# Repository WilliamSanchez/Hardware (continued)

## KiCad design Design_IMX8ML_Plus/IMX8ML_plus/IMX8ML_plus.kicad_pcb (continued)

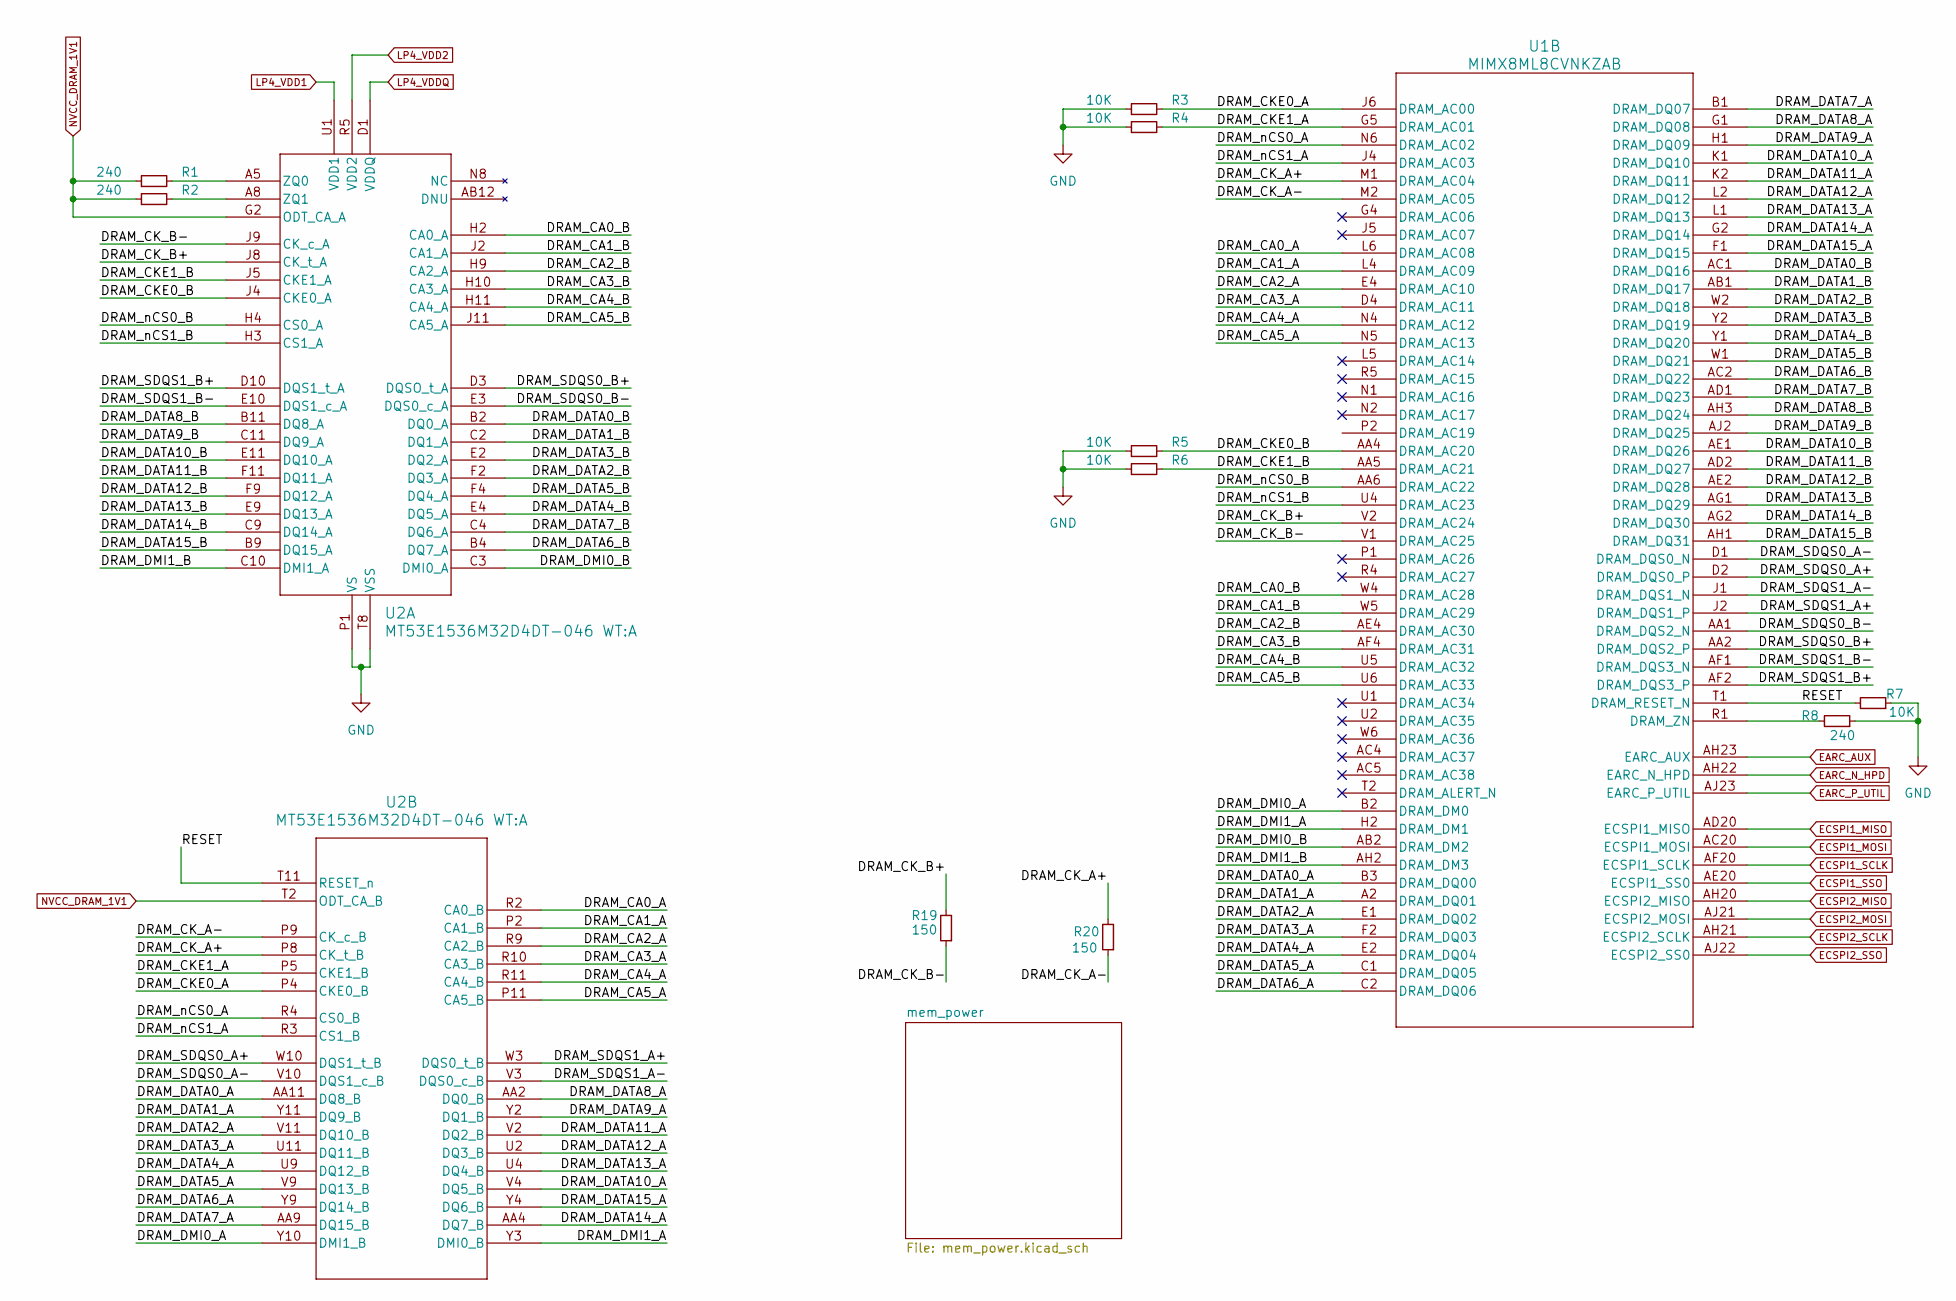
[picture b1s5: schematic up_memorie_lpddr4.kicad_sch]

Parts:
R1, R2, R8: 240; R_0201_0603Metric
R3, R4, R5, R6, R7: 10K; R_0201_0603Metric
R19, R20: 150; R_0201_0603Metric
U1: MIMX8ML8CVNKZAB; LFBGA548_SOT2047-1_NXP
U2: MT53E1536M32D4DT-046 WT:A; VFBGA200_10X14-5_DT_MRN

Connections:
/Processor/Up_memorie_lpddr4/DRAM_CA0_A: U1.L6 (DRAM_AC08), U2.R2 (CA0_B)
/Processor/Up_memorie_lpddr4/DRAM_CA0_B: U1.W4 (DRAM_AC28), U2.H2 (CA0_A)
/Processor/Up_memorie_lpddr4/DRAM_CA1_A: U1.L4 (DRAM_AC09), U2.P2 (CA1_B)
/Processor/Up_memorie_lpddr4/DRAM_CA1_B: U1.W5 (DRAM_AC29), U2.J2 (CA1_A)
/Processor/Up_memorie_lpddr4/DRAM_CA2_A: U1.E4 (DRAM_AC10), U2.R9 (CA2_B)
/Processor/Up_memorie_lpddr4/DRAM_CA2_B: U1.AE4 (DRAM_AC30), U2.H9 (CA2_A)
/Processor/Up_memorie_lpddr4/DRAM_CA3_A: U1.D4 (DRAM_AC11), U2.R10 (CA3_B)
/Processor/Up_memorie_lpddr4/DRAM_CA3_B: U1.AF4 (DRAM_AC31), U2.H10 (CA3_A)
/Processor/Up_memorie_lpddr4/DRAM_CA4_A: U1.N4 (DRAM_AC12), U2.R11 (CA4_B)
/Processor/Up_memorie_lpddr4/DRAM_CA4_B: U1.U5 (DRAM_AC32), U2.H11 (CA4_A)
/Processor/Up_memorie_lpddr4/DRAM_CA5_A: U1.N5 (DRAM_AC13), U2.P11 (CA5_B)
/Processor/Up_memorie_lpddr4/DRAM_CA5_B: U1.U6 (DRAM_AC33), U2.J11 (CA5_A)
/Processor/Up_memorie_lpddr4/DRAM_CKE0_A: R3.2, U1.J6 (DRAM_AC00), U2.P4 (CKE0_B)
/Processor/Up_memorie_lpddr4/DRAM_CKE0_B: R5.2, U1.AA4 (DRAM_AC20), U2.J4 (CKE0_A)
/Processor/Up_memorie_lpddr4/DRAM_CKE1_A: R4.2, U1.G5 (DRAM_AC01), U2.P5 (CKE1_B)
/Processor/Up_memorie_lpddr4/DRAM_CKE1_B: R6.2, U1.AA5 (DRAM_AC21), U2.J5 (CKE1_A)
/Processor/Up_memorie_lpddr4/DRAM_CK_A+: R20.2, U1.M1 (DRAM_AC04), U2.P8 (CK_t_B)
/Processor/Up_memorie_lpddr4/DRAM_CK_A-: R20.1, U1.M2 (DRAM_AC05), U2.P9 (CK_c_B)
/Processor/Up_memorie_lpddr4/DRAM_CK_B+: R19.2, U1.V2 (DRAM_AC24), U2.J8 (CK_t_A)
/Processor/Up_memorie_lpddr4/DRAM_CK_B-: R19.1, U1.V1 (DRAM_AC25), U2.J9 (CK_c_A)
/Processor/Up_memorie_lpddr4/DRAM_DATA0_A: U1.B3 (DRAM_DQ00), U2.AA11 (DQ8_B)
/Processor/Up_memorie_lpddr4/DRAM_DATA0_B: U1.AC1 (DRAM_DQ16), U2.B2 (DQ0_A)
/Processor/Up_memorie_lpddr4/DRAM_DATA1_A: U1.A2 (DRAM_DQ01), U2.Y11 (DQ9_B)
/Processor/Up_memorie_lpddr4/DRAM_DATA1_B: U1.AB1 (DRAM_DQ17), U2.C2 (DQ1_A)
/Processor/Up_memorie_lpddr4/DRAM_DATA2_A: U1.E1 (DRAM_DQ02), U2.V11 (DQ10_B)
/Processor/Up_memorie_lpddr4/DRAM_DATA2_B: U1.W2 (DRAM_DQ18), U2.F2 (DQ3_A)
/Processor/Up_memorie_lpddr4/DRAM_DATA3_A: U1.F2 (DRAM_DQ03), U2.U11 (DQ11_B)
/Processor/Up_memorie_lpddr4/DRAM_DATA3_B: U1.Y2 (DRAM_DQ19), U2.E2 (DQ2_A)
/Processor/Up_memorie_lpddr4/DRAM_DATA4_A: U1.E2 (DRAM_DQ04), U2.U9 (DQ12_B)
/Processor/Up_memorie_lpddr4/DRAM_DATA4_B: U1.Y1 (DRAM_DQ20), U2.E4 (DQ5_A)
/Processor/Up_memorie_lpddr4/DRAM_DATA5_A: U1.C1 (DRAM_DQ05), U2.V9 (DQ13_B)
/Processor/Up_memorie_lpddr4/DRAM_DATA5_B: U1.W1 (DRAM_DQ21), U2.F4 (DQ4_A)
/Processor/Up_memorie_lpddr4/DRAM_DATA6_A: U1.C2 (DRAM_DQ06), U2.Y9 (DQ14_B)
/Processor/Up_memorie_lpddr4/DRAM_DATA6_B: U1.AC2 (DRAM_DQ22), U2.B4 (DQ7_A)
/Processor/Up_memorie_lpddr4/DRAM_DATA7_A: U1.B1 (DRAM_DQ07), U2.AA9 (DQ15_B)
/Processor/Up_memorie_lpddr4/DRAM_DATA7_B: U1.AD1 (DRAM_DQ23), U2.C4 (DQ6_A)
/Processor/Up_memorie_lpddr4/DRAM_DATA8_A: U1.G1 (DRAM_DQ08), U2.AA2 (DQ0_B)
/Processor/Up_memorie_lpddr4/DRAM_DATA8_B: U1.AH3 (DRAM_DQ24), U2.B11 (DQ8_A)
/Processor/Up_memorie_lpddr4/DRAM_DATA9_A: U1.H1 (DRAM_DQ09), U2.Y2 (DQ1_B)
/Processor/Up_memorie_lpddr4/DRAM_DATA9_B: U1.AJ2 (DRAM_DQ25), U2.C11 (DQ9_A)
/Processor/Up_memorie_lpddr4/DRAM_DATA10_A: U1.K1 (DRAM_DQ10), U2.V4 (DQ5_B)
/Processor/Up_memorie_lpddr4/DRAM_DATA10_B: U1.AE1 (DRAM_DQ26), U2.E11 (DQ10_A)
/Processor/Up_memorie_lpddr4/DRAM_DATA11_A: U1.K2 (DRAM_DQ11), U2.V2 (DQ2_B)
/Processor/Up_memorie_lpddr4/DRAM_DATA11_B: U1.AD2 (DRAM_DQ27), U2.F11 (DQ11_A)
/Processor/Up_memorie_lpddr4/DRAM_DATA12_A: U1.L2 (DRAM_DQ12), U2.U2 (DQ3_B)
/Processor/Up_memorie_lpddr4/DRAM_DATA12_B: U1.AE2 (DRAM_DQ28), U2.F9 (DQ12_A)
/Processor/Up_memorie_lpddr4/DRAM_DATA13_A: U1.L1 (DRAM_DQ13), U2.U4 (DQ4_B)
/Processor/Up_memorie_lpddr4/DRAM_DATA13_B: U1.AG1 (DRAM_DQ29), U2.E9 (DQ13_A)
/Processor/Up_memorie_lpddr4/DRAM_DATA14_A: U1.G2 (DRAM_DQ14), U2.AA4 (DQ7_B)
/Processor/Up_memorie_lpddr4/DRAM_DATA14_B: U1.AG2 (DRAM_DQ30), U2.C9 (DQ14_A)
/Processor/Up_memorie_lpddr4/DRAM_DATA15_A: U1.F1 (DRAM_DQ15), U2.Y4 (DQ6_B)
/Processor/Up_memorie_lpddr4/DRAM_DATA15_B: U1.AH1 (DRAM_DQ31), U2.B9 (DQ15_A)
/Processor/Up_memorie_lpddr4/DRAM_DMI0_A: U1.B2 (DRAM_DM0), U2.Y10 (DMI1_B)
/Processor/Up_memorie_lpddr4/DRAM_DMI0_B: U1.AB2 (DRAM_DM2), U2.C3 (DMI0_A)
/Processor/Up_memorie_lpddr4/DRAM_DMI1_A: U1.H2 (DRAM_DM1), U2.Y3 (DMI0_B)
/Processor/Up_memorie_lpddr4/DRAM_DMI1_B: U1.AH2 (DRAM_DM3), U2.C10 (DMI1_A)
/Processor/Up_memorie_lpddr4/DRAM_SDQS0_A+: U1.D2 (DRAM_DQS0_P), U2.W10 (DQS1_t_B)
/Processor/Up_memorie_lpddr4/DRAM_SDQS0_A-: U1.D1 (DRAM_DQS0_N), U2.V10 (DQS1_c_B)
/Processor/Up_memorie_lpddr4/DRAM_SDQS0_B+: U1.AA2 (DRAM_DQS2_P), U2.D3 (DQSO_t_A)
/Processor/Up_memorie_lpddr4/DRAM_SDQS0_B-: U1.AA1 (DRAM_DQS2_N), U2.E3 (DQS0_c_A)
/Processor/Up_memorie_lpddr4/DRAM_SDQS1_A+: U1.J2 (DRAM_DQS1_P), U2.W3 (DQS0_t_B)
/Processor/Up_memorie_lpddr4/DRAM_SDQS1_A-: U1.J1 (DRAM_DQS1_N), U2.V3 (DQS0_c_B)
/Processor/Up_memorie_lpddr4/DRAM_SDQS1_B+: U1.AF2 (DRAM_DQS3_P), U2.D10 (DQS1_t_A)
/Processor/Up_memorie_lpddr4/DRAM_SDQS1_B-: U1.AF1 (DRAM_DQS3_N), U2.E10 (DQS1_c_A)
/Processor/Up_memorie_lpddr4/DRAM_nCS0_A: U1.N6 (DRAM_AC02), U2.R4 (CS0_B)
/Processor/Up_memorie_lpddr4/DRAM_nCS0_B: U1.AA6 (DRAM_AC22), U2.H4 (CS0_A)
/Processor/Up_memorie_lpddr4/DRAM_nCS1_A: U1.J4 (DRAM_AC03), U2.R3 (CS1_B)
/Processor/Up_memorie_lpddr4/DRAM_nCS1_B: U1.U4 (DRAM_AC23), U2.H3 (CS1_A)
/Processor/Up_memorie_lpddr4/RESET: R7.2, U1.T1 (DRAM_RESET_N), U2.T11 (RESET_n)
EARC_AUX: U1.AH23 (EARC_AUX); also elsewhere on the board
EARC_N_HPD: U1.AH22 (EARC_N_HPD); also elsewhere on the board
EARC_P_UTIL: U1.AJ23 (EARC_P_UTIL); also elsewhere on the board
ECSPI1_MISO: U1.AD20 (ECSPI1_MISO); also elsewhere on the board
ECSPI1_MOSI: U1.AC20 (ECSPI1_MOSI); also elsewhere on the board
ECSPI1_SCLK: U1.AF20 (ECSPI1_SCLK); also elsewhere on the board
ECSPI1_SSO: U1.AE20 (ECSPI1_SS0); also elsewhere on the board
ECSPI2_MISO: U1.AH20 (ECSPI2_MISO); also elsewhere on the board
ECSPI2_MOSI: U1.AJ21 (ECSPI2_MOSI); also elsewhere on the board
ECSPI2_SCLK: U1.AH21 (ECSPI2_SCLK); also elsewhere on the board
ECSPI2_SSO: U1.AJ22 (ECSPI2_SS0); also elsewhere on the board
GND: R3.1, R4.1, R5.1, R6.1, R7.1, R8.1, U2.A3 (VSS), U2.A10 (VSS), U2.AB3 (VSS), U2.AB5 (VSS), U2.AB8 (VSS), U2.AB10 (VSS), U2.C1 (VSS), U2.C5 (VSS), U2.C8 (VSS), U2.C12 (VSS), U2.D2 (VSS), U2.D4 (VSS), U2.D9 (VSS), U2.D11 (VSS), U2.E1 (VSS), U2.E5 (VSS), U2.E8 (VSS), U2.E12 (VSS), U2.G1 (VSS), U2.G3 (VSS), U2.G5 (VSS), U2.G8 (VSS), U2.G10 (VSS), U2.G12 (VSS), U2.J1 (VSS), U2.J3 (VSS), U2.J10 (VSS), U2.J12 (VSS), U2.K2 (VSS), U2.K4 (VSS), U2.K9 (VSS), U2.K11 (VSS), U2.N2 (VSS), U2.N4 (VSS), U2.N9 (VSS), U2.N11 (VSS), U2.P1 (VS), U2.P3 (VSS), U2.P10 (VSS), U2.P12 (VSS), U2.T1 (VSS), U2.T3 (VSS), U2.T5 (VSS), U2.T8 (VSS), U2.T10 (VSS), U2.T12 (VSS), U2.V1 (VSS), U2.V5 (VSS), U2.V8 (VSS), U2.V12 (VSS), U2.W2 (VSS), U2.W4 (VSS), U2.W9 (VSS), U2.W11 (VSS), U2.Y1 (VSS), U2.Y5 (VSS), U2.Y8 (VSS), U2.Y12 (VSS); also elsewhere on the board
LP4_VDD1: U2.F1 (VDD1), U2.F12 (VDD1), U2.G4 (VDD1), U2.G9 (VDD1), U2.T4 (VDD1), U2.T9 (VDD1), U2.U1 (VDD1), U2.U12 (VDD1); also elsewhere on the board
LP4_VDD2: R1.1, R2.1, U2.A4 (VDD2), U2.A9 (VDD2), U2.AA3 (VDDQ), U2.AA5 (VDDQ), U2.AA8 (VDDQ), U2.AA10 (VDDQ), U2.AB4 (VDD2), U2.AB9 (VDD2), U2.B3 (VDDQ), U2.B5 (VDDQ), U2.B8 (VDDQ), U2.B10 (VDDQ), U2.D1 (VDDQ), U2.D5 (VDDQ), U2.D8 (VDDQ), U2.D12 (VDDQ), U2.F3 (VDDQ), U2.F5 (VDD2), U2.F8 (VDD2), U2.F10 (VDDQ), U2.G2 (ODT_CA_A), U2.H1 (VDD2), U2.H5 (VDD2), U2.H8 (VDD2), U2.H12 (VDD2), U2.K1 (VDD2), U2.K3 (VDD2), U2.K10 (VDD2), U2.K12 (VDD2), U2.N1 (VDD2), U2.N3 (VDD2), U2.N10 (VDD2), U2.N12 (VDD2), U2.R1 (VDD2), U2.R5 (VDD2), U2.R8 (VDD2), U2.R12 (VDD2), U2.T2 (ODT_CA_B), U2.U3 (VDDQ), U2.U5 (VDD2), U2.U8 (VDD2), U2.U10 (VDDQ), U2.W1 (VDDQ), U2.W5 (VDDQ), U2.W8 (VDDQ), U2.W12 (VDDQ); also elsewhere on the board
unnamed: R8.2, U1.R1 (DRAM_ZN)
unnamed: R1.2, U2.A5 (ZQ0)
unnamed: R2.2, U2.A8 (ZQ1)

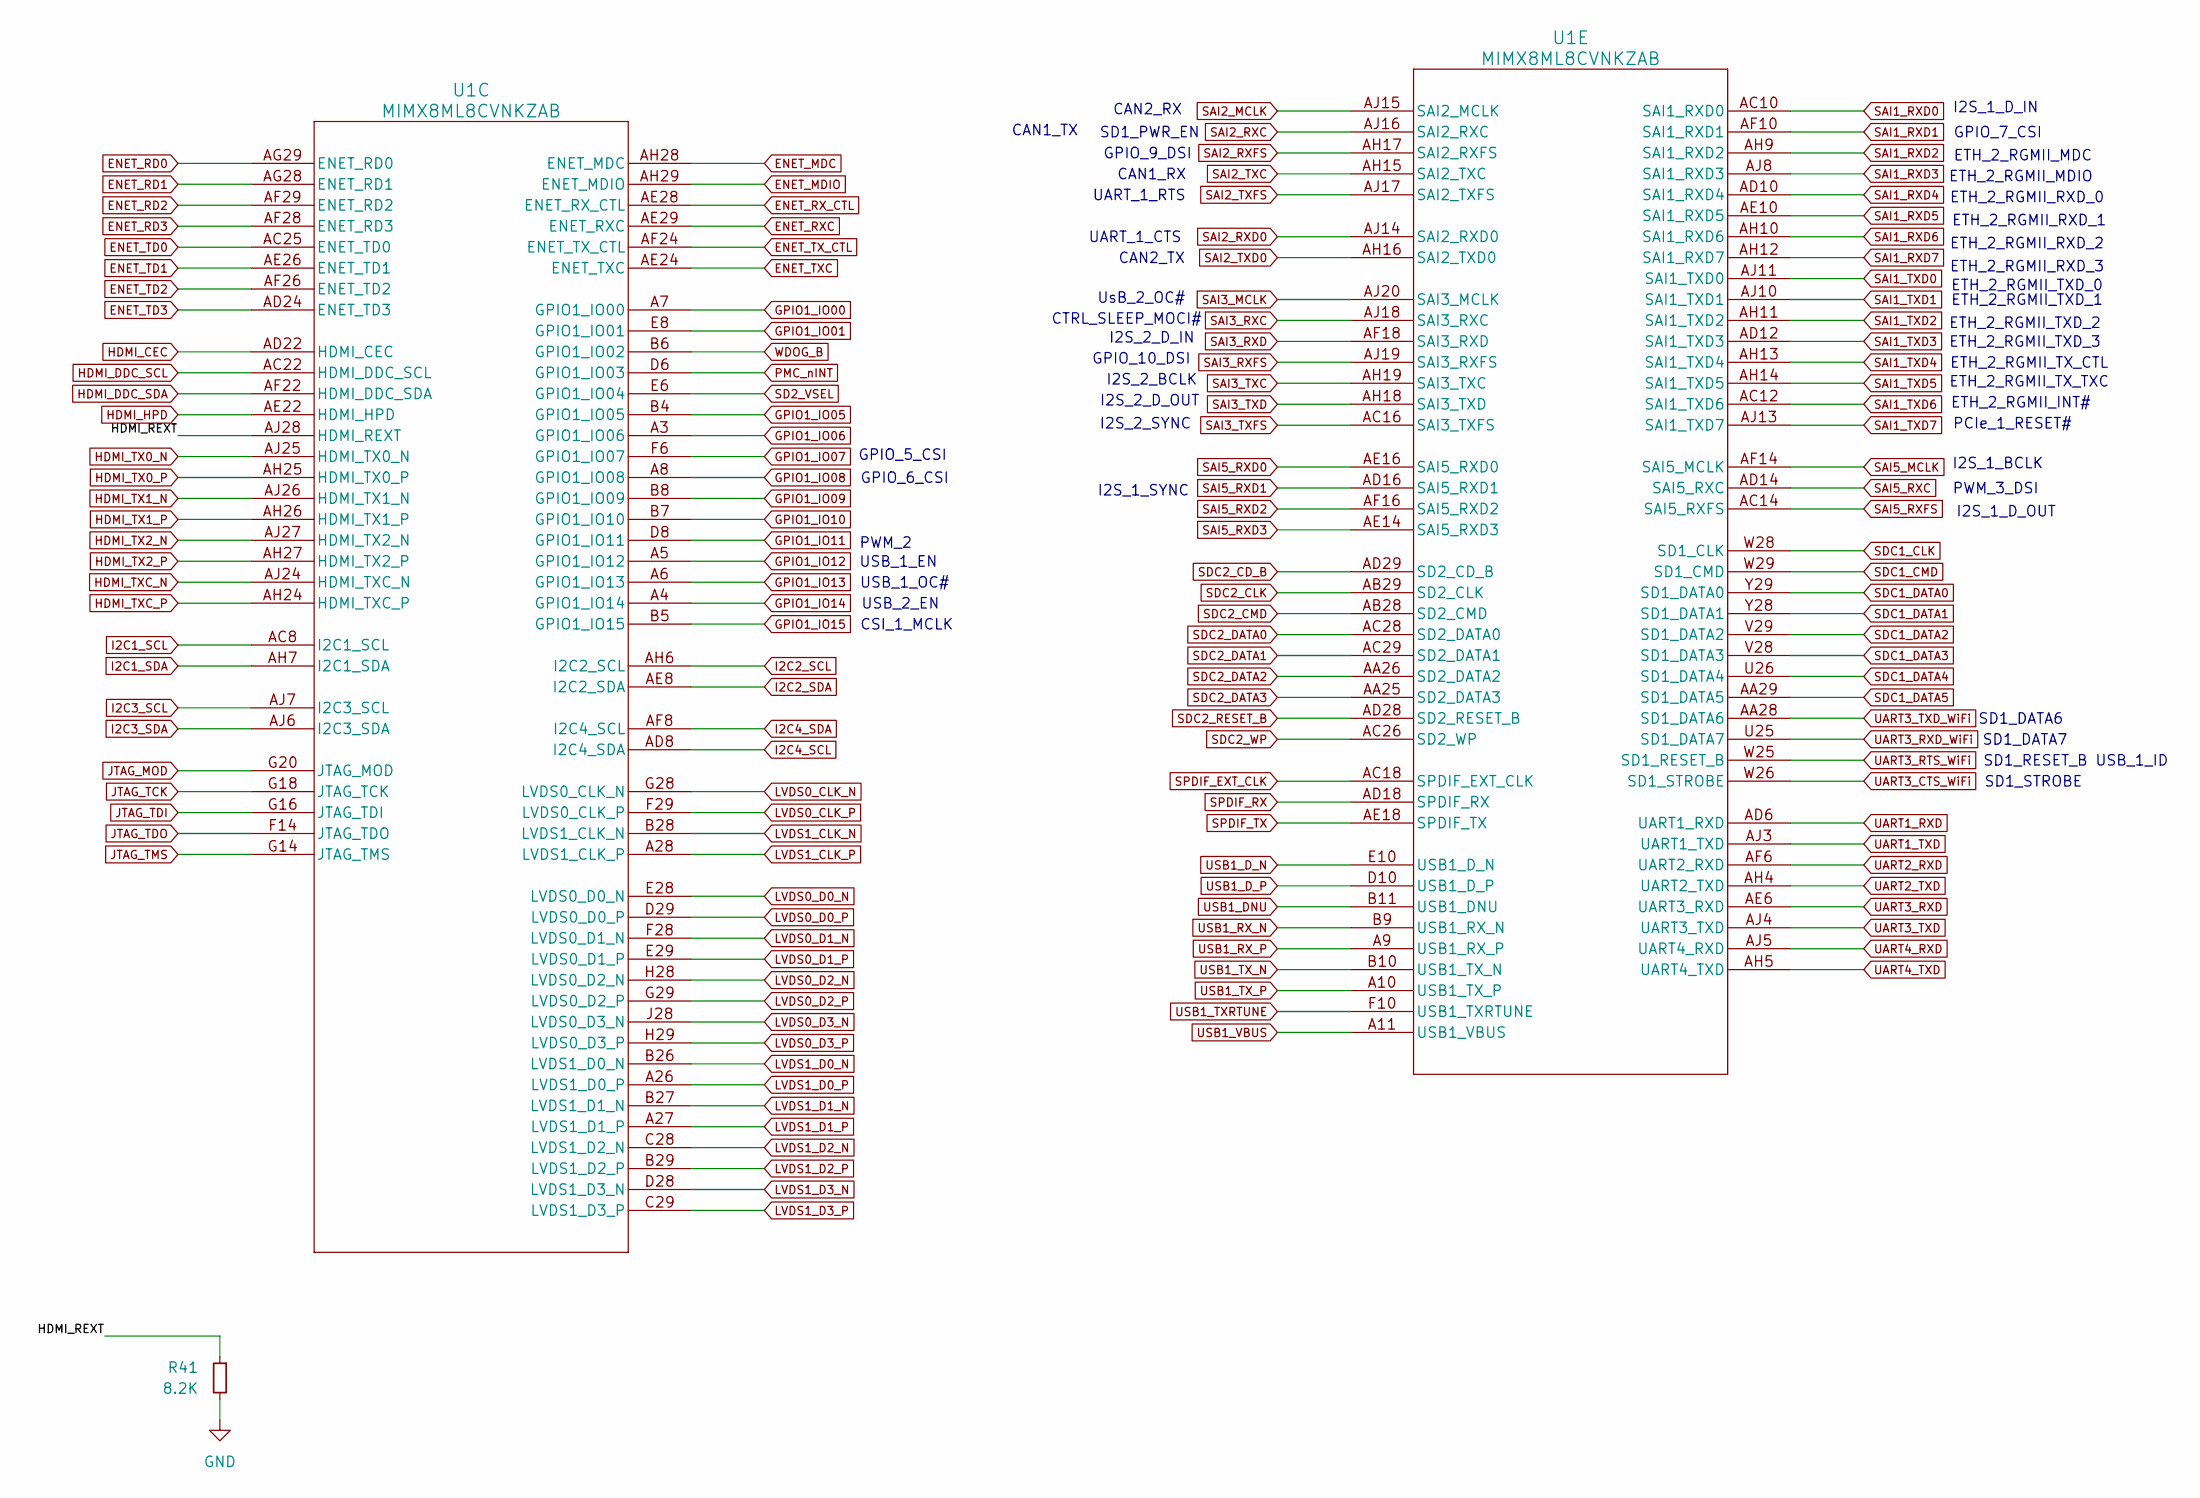
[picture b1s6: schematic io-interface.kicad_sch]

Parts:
R41: 8.2K; R_0201_0603Metric
U1: MIMX8ML8CVNKZAB; LFBGA548_SOT2047-1_NXP

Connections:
/Processor/io-interface/<NO NET>: R41.1, U1.AJ28 (HDMI_REXT)
ENET_MDC: U1.AH28 (ENET_MDC); also elsewhere on the board
ENET_MDIO: U1.AH29 (ENET_MDIO); also elsewhere on the board
ENET_RD0: U1.AG29 (ENET_RD0); also elsewhere on the board
ENET_RD1: U1.AG28 (ENET_RD1); also elsewhere on the board
ENET_RD2: U1.AF29 (ENET_RD2); also elsewhere on the board
ENET_RD3: U1.AF28 (ENET_RD3); also elsewhere on the board
ENET_RXC: U1.AE29 (ENET_RXC); also elsewhere on the board
ENET_RX_CTL: U1.AE28 (ENET_RX_CTL); also elsewhere on the board
ENET_TD0: U1.AC25 (ENET_TD0); also elsewhere on the board
ENET_TD1: U1.AE26 (ENET_TD1); also elsewhere on the board
ENET_TD2: U1.AF26 (ENET_TD2); also elsewhere on the board
ENET_TD3: U1.AD24 (ENET_TD3); also elsewhere on the board
ENET_TXC: U1.AE24 (ENET_TXC); also elsewhere on the board
ENET_TX_CTL: U1.AF24 (ENET_TX_CTL); also elsewhere on the board
GND: R41.2; also elsewhere on the board
GPIO1_IO00: U1.A7 (GPIO1_IO00); also elsewhere on the board
GPIO1_IO01: U1.E8 (GPIO1_IO01); also elsewhere on the board
GPIO1_IO05: U1.B4 (GPIO1_IO05); also elsewhere on the board
GPIO1_IO06: U1.A3 (GPIO1_IO06); also elsewhere on the board
GPIO1_IO07: U1.F6 (GPIO1_IO07); also elsewhere on the board
GPIO1_IO08: U1.A8 (GPIO1_IO08); also elsewhere on the board
GPIO1_IO09: U1.B8 (GPIO1_IO09); also elsewhere on the board
GPIO1_IO10: U1.B7 (GPIO1_IO10); also elsewhere on the board
GPIO1_IO11: U1.D8 (GPIO1_IO11); also elsewhere on the board
GPIO1_IO12: U1.A5 (GPIO1_IO12); also elsewhere on the board
GPIO1_IO13: U1.A6 (GPIO1_IO13); also elsewhere on the board
GPIO1_IO14: U1.A4 (GPIO1_IO14); also elsewhere on the board
GPIO1_IO15: U1.B5 (GPIO1_IO15); also elsewhere on the board
HDMI_CEC: U1.AD22 (HDMI_CEC); also elsewhere on the board
HDMI_DDC_SCL: U1.AC22 (HDMI_DDC_SCL); also elsewhere on the board
HDMI_DDC_SDA: U1.AF22 (HDMI_DDC_SDA); also elsewhere on the board
HDMI_HPD: U1.AE22 (HDMI_HPD); also elsewhere on the board
HDMI_TX0_N: U1.AJ25 (HDMI_TX0_N); also elsewhere on the board
HDMI_TX0_P: U1.AH25 (HDMI_TX0_P); also elsewhere on the board
HDMI_TX1_N: U1.AJ26 (HDMI_TX1_N); also elsewhere on the board
HDMI_TX1_P: U1.AH26 (HDMI_TX1_P); also elsewhere on the board
HDMI_TX2_N: U1.AJ27 (HDMI_TX2_N); also elsewhere on the board
HDMI_TX2_P: U1.AH27 (HDMI_TX2_P); also elsewhere on the board
HDMI_TXC_N: U1.AJ24 (HDMI_TXC_N); also elsewhere on the board
HDMI_TXC_P: U1.AH24 (HDMI_TXC_P); also elsewhere on the board
I2C1_SCL: U1.AC8 (I2C1_SCL); also elsewhere on the board
I2C1_SDA: U1.AH7 (I2C1_SDA); also elsewhere on the board
I2C2_SCL: U1.AH6 (I2C2_SCL); also elsewhere on the board
I2C2_SDA: U1.AE8 (I2C2_SDA); also elsewhere on the board
I2C3_SCL: U1.AJ7 (I2C3_SCL); also elsewhere on the board
I2C3_SDA: U1.AJ6 (I2C3_SDA); also elsewhere on the board
I2C4_SCL: U1.AD8 (I2C4_SDA); also elsewhere on the board
I2C4_SDA: U1.AF8 (I2C4_SCL); also elsewhere on the board
JTAG_MOD: U1.G20 (JTAG_MOD); also elsewhere on the board
JTAG_TCK: U1.G18 (JTAG_TCK); also elsewhere on the board
JTAG_TDI: U1.G16 (JTAG_TDI); also elsewhere on the board
JTAG_TDO: U1.F14 (JTAG_TDO); also elsewhere on the board
JTAG_TMS: U1.G14 (JTAG_TMS); also elsewhere on the board
LVDS0_CLK_N: U1.G28 (LVDS0_CLK_N); also elsewhere on the board
LVDS0_CLK_P: U1.F29 (LVDS0_CLK_P); also elsewhere on the board
LVDS0_D0_N: U1.E28 (LVDS0_D0_N); also elsewhere on the board
LVDS0_D0_P: U1.D29 (LVDS0_D0_P); also elsewhere on the board
LVDS0_D1_N: U1.F28 (LVDS0_D1_N); also elsewhere on the board
LVDS0_D1_P: U1.E29 (LVDS0_D1_P); also elsewhere on the board
LVDS0_D2_N: U1.H28 (LVDS0_D2_N); also elsewhere on the board
LVDS0_D2_P: U1.G29 (LVDS0_D2_P); also elsewhere on the board
LVDS0_D3_N: U1.J28 (LVDS0_D3_N); also elsewhere on the board
LVDS0_D3_P: U1.H29 (LVDS0_D3_P); also elsewhere on the board
LVDS1_CLK_N: U1.B28 (LVDS1_CLK_N); also elsewhere on the board
LVDS1_CLK_P: U1.A28 (LVDS1_CLK_P); also elsewhere on the board
LVDS1_D0_N: U1.B26 (LVDS1_D0_N); also elsewhere on the board
LVDS1_D0_P: U1.A26 (LVDS1_D0_P); also elsewhere on the board
LVDS1_D1_N: U1.B27 (LVDS1_D1_N); also elsewhere on the board
LVDS1_D1_P: U1.A27 (LVDS1_D1_P); also elsewhere on the board
LVDS1_D2_N: U1.C28 (LVDS1_D2_N); also elsewhere on the board
LVDS1_D2_P: U1.B29 (LVDS1_D2_P); also elsewhere on the board
LVDS1_D3_N: U1.D28 (LVDS1_D3_N); also elsewhere on the board
LVDS1_D3_P: U1.C29 (LVDS1_D3_P); also elsewhere on the board
PMC_nINT: U1.D6 (GPIO1_IO03); also elsewhere on the board
SAI1_RXD0: U1.AC10 (SAI1_RXD0); also elsewhere on the board
SAI1_RXD1: U1.AF10 (SAI1_RXD1); also elsewhere on the board
SAI1_RXD2: U1.AH9 (SAI1_RXD2); also elsewhere on the board
SAI1_RXD3: U1.AJ8 (SAI1_RXD3); also elsewhere on the board
SAI1_RXD4: U1.AD10 (SAI1_RXD4); also elsewhere on the board
SAI1_RXD5: U1.AE10 (SAI1_RXD5); also elsewhere on the board
SAI1_RXD6: U1.AH10 (SAI1_RXD6); also elsewhere on the board
SAI1_RXD7: U1.AH12 (SAI1_RXD7); also elsewhere on the board
SAI1_TXD0: U1.AJ11 (SAI1_TXD0); also elsewhere on the board
SAI1_TXD1: U1.AJ10 (SAI1_TXD1); also elsewhere on the board
SAI1_TXD2: U1.AH11 (SAI1_TXD2); also elsewhere on the board
SAI1_TXD3: U1.AD12 (SAI1_TXD3); also elsewhere on the board
SAI1_TXD4: U1.AH13 (SAI1_TXD4); also elsewhere on the board
SAI1_TXD5: U1.AH14 (SAI1_TXD5); also elsewhere on the board
SAI1_TXD6: U1.AC12 (SAI1_TXD6); also elsewhere on the board
SAI1_TXD7: U1.AJ13 (SAI1_TXD7); also elsewhere on the board
SAI2_MCLK: U1.AJ15 (SAI2_MCLK); also elsewhere on the board
SAI2_RXC: U1.AJ16 (SAI2_RXC); also elsewhere on the board
SAI2_RXD0: U1.AJ14 (SAI2_RXD0); also elsewhere on the board
SAI2_RXFS: U1.AH17 (SAI2_RXFS); also elsewhere on the board
SAI2_TXC: U1.AH15 (SAI2_TXC); also elsewhere on the board
SAI2_TXD0: U1.AH16 (SAI2_TXD0); also elsewhere on the board
SAI2_TXFS: U1.AJ17 (SAI2_TXFS); also elsewhere on the board
SAI3_MCLK: U1.AJ20 (SAI3_MCLK); also elsewhere on the board
SAI3_RXC: U1.AJ18 (SAI3_RXC); also elsewhere on the board
SAI3_RXD: U1.AF18 (SAI3_RXD); also elsewhere on the board
SAI3_RXFS: U1.AJ19 (SAI3_RXFS); also elsewhere on the board
SAI3_TXC: U1.AH19 (SAI3_TXC); also elsewhere on the board
SAI3_TXD: U1.AH18 (SAI3_TXD); also elsewhere on the board
SAI3_TXFS: U1.AC16 (SAI3_TXFS); also elsewhere on the board
SAI5_MCLK: U1.AF14 (SAI5_MCLK); also elsewhere on the board
SAI5_RXC: U1.AD14 (SAI5_RXC); also elsewhere on the board
SAI5_RXD0: U1.AE16 (SAI5_RXD0); also elsewhere on the board
SAI5_RXD1: U1.AD16 (SAI5_RXD1); also elsewhere on the board
SAI5_RXD2: U1.AF16 (SAI5_RXD2); also elsewhere on the board
SAI5_RXD3: U1.AE14 (SAI5_RXD3); also elsewhere on the board
SAI5_RXFS: U1.AC14 (SAI5_RXFS); also elsewhere on the board
SD2_VSEL: U1.E6 (GPIO1_IO04); also elsewhere on the board
SDC1_CLK: U1.W28 (SD1_CLK); also elsewhere on the board
SDC1_CMD: U1.W29 (SD1_CMD); also elsewhere on the board
SDC1_DATA0: U1.Y29 (SD1_DATA0); also elsewhere on the board
SDC1_DATA1: U1.Y28 (SD1_DATA1); also elsewhere on the board
SDC1_DATA2: U1.V29 (SD1_DATA2); also elsewhere on the board
SDC1_DATA3: U1.V28 (SD1_DATA3); also elsewhere on the board
SDC1_DATA4: U1.U26 (SD1_DATA4)
SDC1_DATA5: U1.AA29 (SD1_DATA5)
SDC2_CD_B: U1.AD29 (SD2_CD_B); also elsewhere on the board
SDC2_CLK: U1.AB29 (SD2_CLK); also elsewhere on the board
SDC2_CMD: U1.AB28 (SD2_CMD); also elsewhere on the board
SDC2_DATA0: U1.AC28 (SD2_DATA0); also elsewhere on the board
SDC2_DATA1: U1.AC29 (SD2_DATA1); also elsewhere on the board
SDC2_DATA2: U1.AA26 (SD2_DATA2); also elsewhere on the board
SDC2_DATA3: U1.AA25 (SD2_DATA3); also elsewhere on the board
SDC2_RESET_B: U1.AD28 (SD2_RESET_B); also elsewhere on the board
SDC2_WP: U1.AC26 (SD2_WP); also elsewhere on the board
SPDIF_EXT_CLK: U1.AC18 (SPDIF_EXT_CLK); also elsewhere on the board
SPDIF_RX: U1.AD18 (SPDIF_RX); also elsewhere on the board
SPDIF_TX: U1.AE18 (SPDIF_TX); also elsewhere on the board
UART1_RXD: U1.AD6 (UART1_RXD); also elsewhere on the board
UART1_TXD: U1.AJ3 (UART1_TXD); also elsewhere on the board
UART2_RXD: U1.AF6 (UART2_RXD); also elsewhere on the board
UART2_TXD: U1.AH4 (UART2_TXD); also elsewhere on the board
UART3_CTS_WiFi: U1.W26 (SD1_STROBE); also elsewhere on the board
UART3_RTS_WiFi: U1.W25 (SD1_RESET_B); also elsewhere on the board
UART3_RXD: U1.AE6 (UART3_RXD)
UART3_RXD_WiFi: U1.U25 (SD1_DATA7); also elsewhere on the board
UART3_TXD: U1.AJ4 (UART3_TXD)
UART3_TXD_WiFi: U1.AA28 (SD1_DATA6); also elsewhere on the board
UART4_RXD: U1.AJ5 (UART4_RXD); also elsewhere on the board
UART4_TXD: U1.AH5 (UART4_TXD); also elsewhere on the board
USB1_DNU: U1.B11 (USB1_DNU)
USB1_D_N: U1.E10 (USB1_D_N); also elsewhere on the board
USB1_D_P: U1.D10 (USB1_D_P); also elsewhere on the board
USB1_RX_N: U1.B9 (USB1_RX_N); also elsewhere on the board
USB1_RX_P: U1.A9 (USB1_RX_P); also elsewhere on the board
USB1_TXRTUNE: U1.F10 (USB1_TXRTUNE)
USB1_TX_N: U1.B10 (USB1_TX_N); also elsewhere on the board
USB1_TX_P: U1.A10 (USB1_TX_P); also elsewhere on the board
USB1_VBUS: U1.A11 (USB1_VBUS); also elsewhere on the board
WDOG_B: U1.B6 (GPIO1_IO02); also elsewhere on the board

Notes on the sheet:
CSI_1_MCLK
ETH_2_RGMII_TXD_2
I2S_1_BCLK
SD1_DATA6
CAN2_RX
CAN2_TX
SD1_STROBE
I2S_2_SYNC
PWM_3_DSI
GPIO_5_CSI
PCIe_1_RESET#
ETH_2_RGMII_INT#
ETH_2_RGMII_RXD_0
ETH_2_RGMII_RXD_2
UART_1_CTS
ETH_2_RGMII_TXD_3
SD1_RESET_B
ETH_2_RGMII_TX_TXC
UART_1_RTS
CAN1_RX
ETH_2_RGMII_MDIO
GPIO_6_CSI
PWM_2
I2S_1_D_OUT
I2S_1_D_IN
USB_1_OC#
GPIO_10_DSI
ETH_2_RGMII_TX_CTL
SD1_PWR_EN
ETH_2_RGMII_MDC
GPIO_9_DSI
CAN1_TX
ETH_2_RGMII_TXD_0
I2S_1_SYNC
CTRL_SLEEP_MOCI#
USB_1_EN
ETH_2_RGMII_RXD_1
UsB_2_OC#
USB_2_EN
ETH_2_RGMII_RXD_3

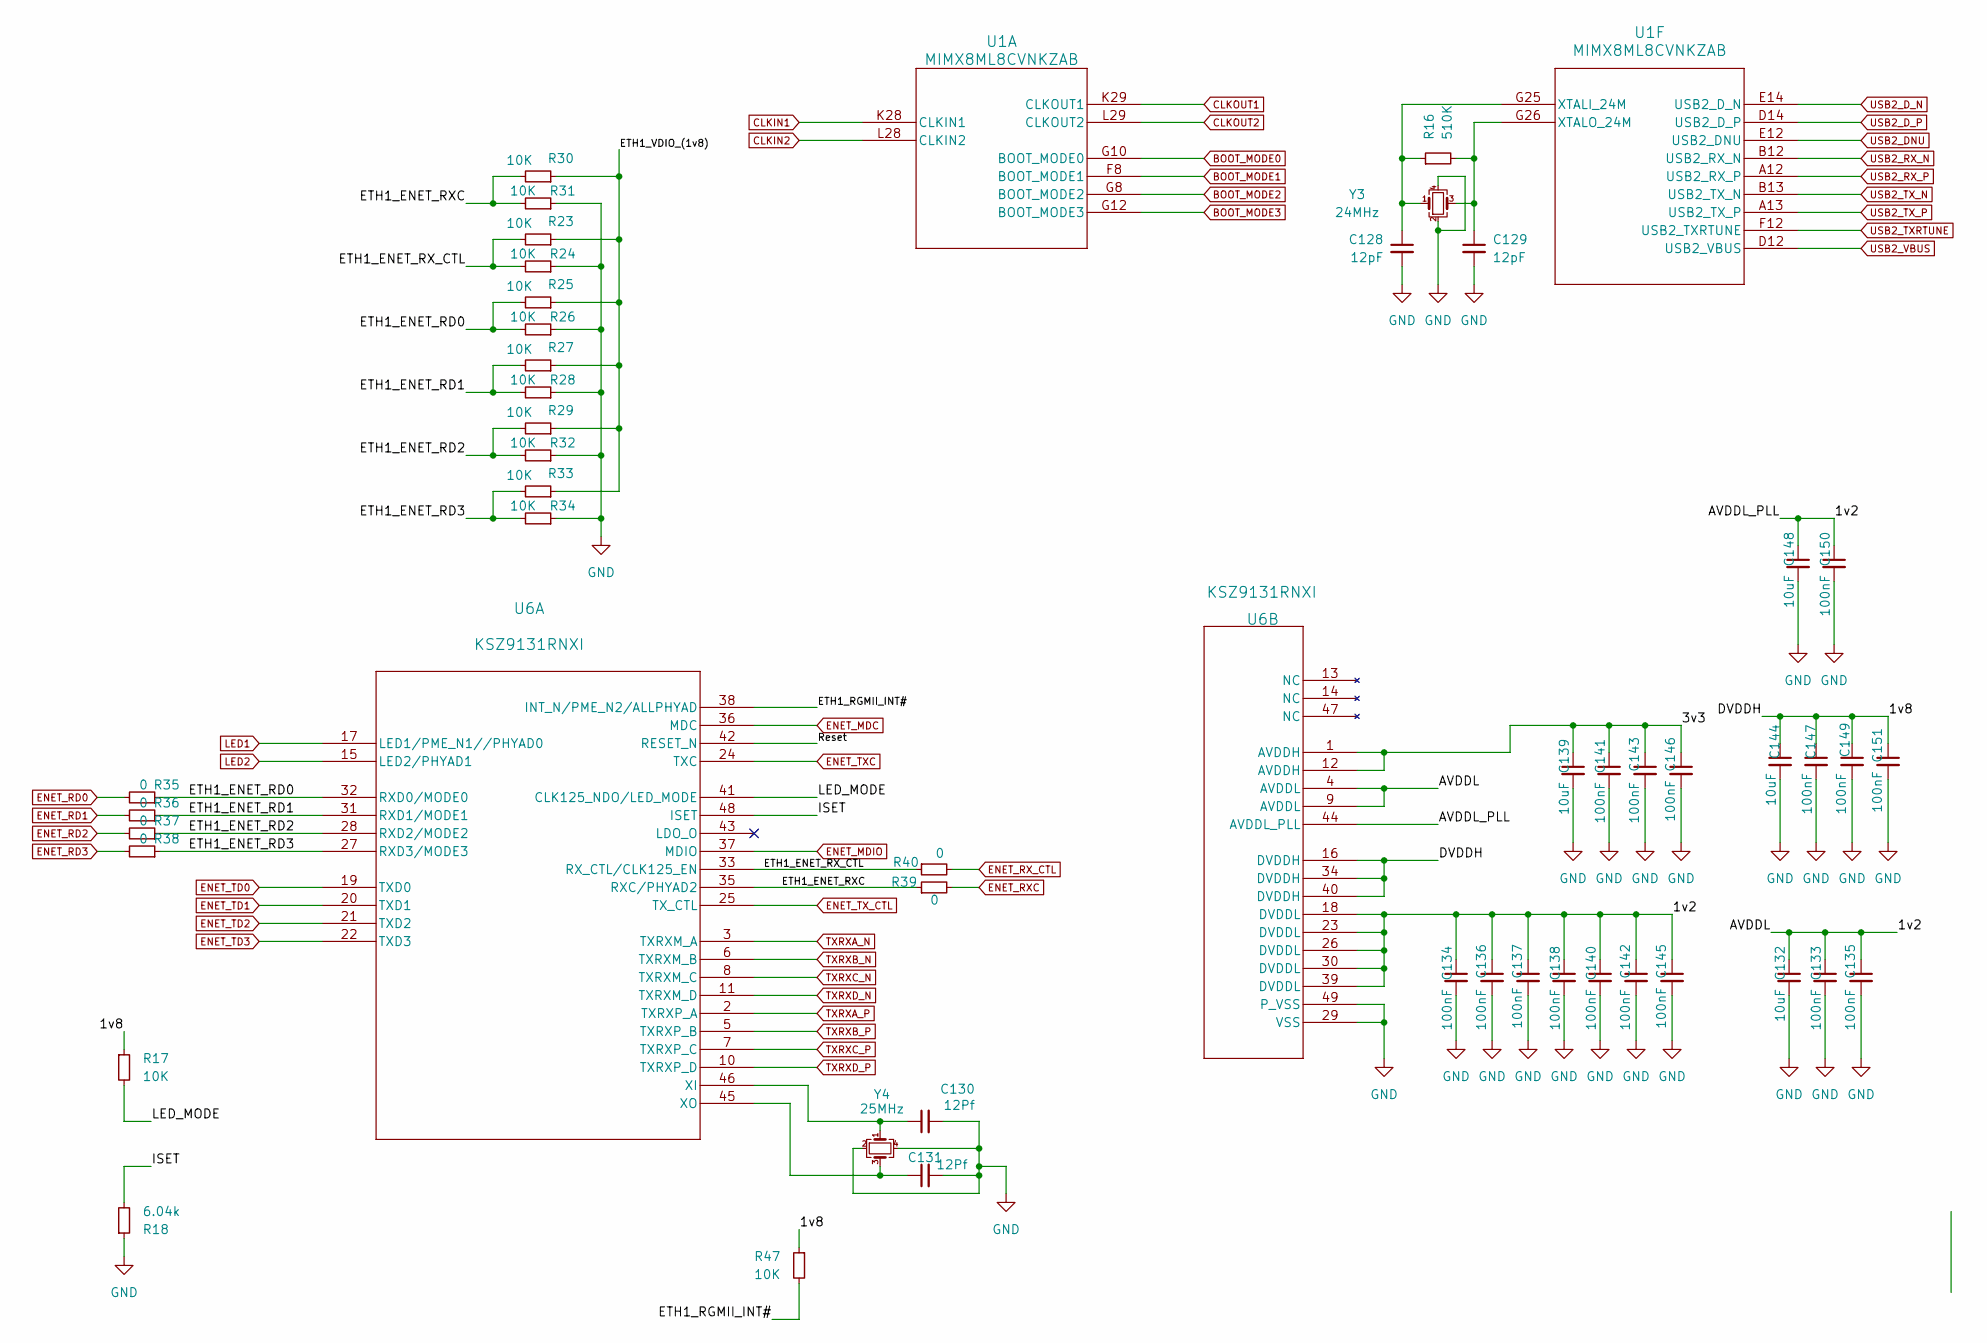
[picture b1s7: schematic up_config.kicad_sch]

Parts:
C128, C129: 12pF; C_0201_0603Metric
C130, C131: 12Pf; C_0402_1005Metric
C132, C139, C144, C148: 10uF; C_0402_1005Metric
C133, C134, C135, C136, C137, C138, C140, C141, C142, C143, C145, C146, C147, C149, C150, C151: 100nF; C_0402_1005Metric
R16: 510K; R_0402_1005Metric
R17, R23, R24, R25, R26, R27, R28, R29, R30, R31, R32, R33, R34, R47: 10K; R_0402_1005Metric
R18: 6.04k; R_0402_1005Metric
R35, R36, R37, R38, R39, R40: 0; R_0402_1005Metric
U1: MIMX8ML8CVNKZAB; LFBGA548_SOT2047-1_NXP
U6: KSZ9131RNXI; QFN-48-1EP_7x7mm_P0.5mm_EP5.6x5.6mm
Y3: 24MHz; Crystal_SMD_3225-4Pin_3.2x2.5mm
Y4: 25MHz; Crystal_SMD_3225-4Pin_3.2x2.5mm

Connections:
/Processor/up_config/1v2: C132.1, C133.1, C134.1, C135.1, C136.1, C137.1, C138.1, C140.1, C142.1, C145.1, C148.1, C150.1, U6.4 (AVDDL), U6.9 (AVDDL), U6.18 (DVDDL), U6.23 (DVDDL), U6.26 (DVDDL), U6.30 (DVDDL), U6.39 (DVDDL), U6.44 (AVDDL_PLL)
/Processor/up_config/1v8: C144.1, C147.1, C149.1, C151.1, R17.1, R47.1, U6.16 (DVDDH), U6.34 (DVDDH), U6.40 (DVDDH)
/Processor/up_config/3v3: C139.1, C141.1, C143.1, C146.1, U6.1 (AVDDH), U6.12 (AVDDH)
/Processor/up_config/ETH1_ENET_RD0: R25.2, R26.2, R35.1, U6.32 (RXD0/MODE0)
/Processor/up_config/ETH1_ENET_RD1: R27.2, R28.2, R36.1, U6.31 (RXD1/MODE1)
/Processor/up_config/ETH1_ENET_RD2: R29.2, R32.2, R37.1, U6.28 (RXD2/MODE2)
/Processor/up_config/ETH1_ENET_RD3: R33.2, R34.2, R38.1, U6.27 (RXD3/MODE3)
/Processor/up_config/ETH1_ENET_RXC: R30.2, R31.2, R39.1, U6.35 (RXC/PHYAD2)
/Processor/up_config/ETH1_ENET_RX_CTL: R23.2, R24.2, R40.1, U6.33 (RX_CTL/CLK125_EN)
/Processor/up_config/ETH1_RGMII_INT#: R47.2, U6.38 (INT_N/PME_N2/ALLPHYAD)
/Processor/up_config/ETH1_VDIO_(1v8): R23.1, R25.1, R27.1, R29.1, R30.1, R33.1
/Processor/up_config/ISET: R18.2, U6.48 (ISET)
/Processor/up_config/LED_MODE: R17.2, U6.41 (CLK125_NDO/LED_MODE)
/Processor/up_config/Reset: U6.42 (RESET_N)
BOOT_MODE0: U1.G10 (BOOT_MODE0); also elsewhere on the board
BOOT_MODE1: U1.F8 (BOOT_MODE1); also elsewhere on the board
BOOT_MODE2: U1.G8 (BOOT_MODE2); also elsewhere on the board
BOOT_MODE3: U1.G12 (BOOT_MODE3); also elsewhere on the board
CLKIN1: U1.K28 (CLKIN1); also elsewhere on the board
CLKIN2: U1.L28 (CLKIN2); also elsewhere on the board
CLKOUT1: U1.K29 (CLKOUT1); also elsewhere on the board
CLKOUT2: U1.L29 (CLKOUT2); also elsewhere on the board
ENET_MDC: U6.36 (MDC); also elsewhere on the board
ENET_MDIO: U6.37 (MDIO); also elsewhere on the board
ENET_RD0: R35.2; also elsewhere on the board
ENET_RD1: R36.2; also elsewhere on the board
ENET_RD2: R37.2; also elsewhere on the board
ENET_RD3: R38.2; also elsewhere on the board
ENET_RXC: R39.2; also elsewhere on the board
ENET_RX_CTL: R40.2; also elsewhere on the board
ENET_TD0: U6.19 (TXD0); also elsewhere on the board
ENET_TD1: U6.20 (TXD1); also elsewhere on the board
ENET_TD2: U6.21 (TXD2); also elsewhere on the board
ENET_TD3: U6.22 (TXD3); also elsewhere on the board
ENET_TXC: U6.24 (TXC); also elsewhere on the board
ENET_TX_CTL: U6.25 (TX_CTL); also elsewhere on the board
GND: C128.2, C129.2, C130.2, C131.2, C132.2, C133.2, C134.2, C135.2, C136.2, C137.2, C138.2, C139.2, C140.2, C141.2, C142.2, C143.2, C144.2, C145.2, C146.2, C147.2, C148.2, C149.2, C150.2, C151.2, R18.1, R24.1, R26.1, R28.1, R31.1, R32.1, R34.1, U6.29 (VSS), U6.49 (P_VSS), Y3.2, Y3.4, Y4.2, Y4.4; also elsewhere on the board
LED1: U6.17 (LED1/PME_N1//PHYAD0); also elsewhere on the board
LED2: U6.15 (LED2/PHYAD1); also elsewhere on the board
unnamed: C128.1, R16.1, U1.G25 (XTALI_24M), Y3.1
unnamed: C129.1, R16.2, U1.G26 (XTALO_24M), Y3.3
unnamed: C130.1, U6.46 (XI), Y4.1
unnamed: C131.1, U6.45 (XO), Y4.3
TXRXA_N: U6.3 (TXRXM_A); also elsewhere on the board
TXRXA_P: U6.2 (TXRXP_A); also elsewhere on the board
TXRXB_N: U6.6 (TXRXM_B); also elsewhere on the board
TXRXB_P: U6.5 (TXRXP_B); also elsewhere on the board
TXRXC_N: U6.8 (TXRXM_C); also elsewhere on the board
TXRXC_P: U6.7 (TXRXP_C); also elsewhere on the board
TXRXD_N: U6.11 (TXRXM_D); also elsewhere on the board
TXRXD_P: U6.10 (TXRXP_D); also elsewhere on the board
USB2_DNU: U1.E12 (USB2_DNU)
USB2_D_N: U1.E14 (USB2_D_N); also elsewhere on the board
USB2_D_P: U1.D14 (USB2_D_P); also elsewhere on the board
USB2_RX_N: U1.B12 (USB2_RX_N); also elsewhere on the board
USB2_RX_P: U1.A12 (USB2_RX_P); also elsewhere on the board
USB2_TXRTUNE: U1.F12 (USB2_TXRTUNE)
USB2_TX_N: U1.B13 (USB2_TX_N); also elsewhere on the board
USB2_TX_P: U1.A13 (USB2_TX_P); also elsewhere on the board
USB2_VBUS: U1.D12 (USB2_VBUS); also elsewhere on the board
